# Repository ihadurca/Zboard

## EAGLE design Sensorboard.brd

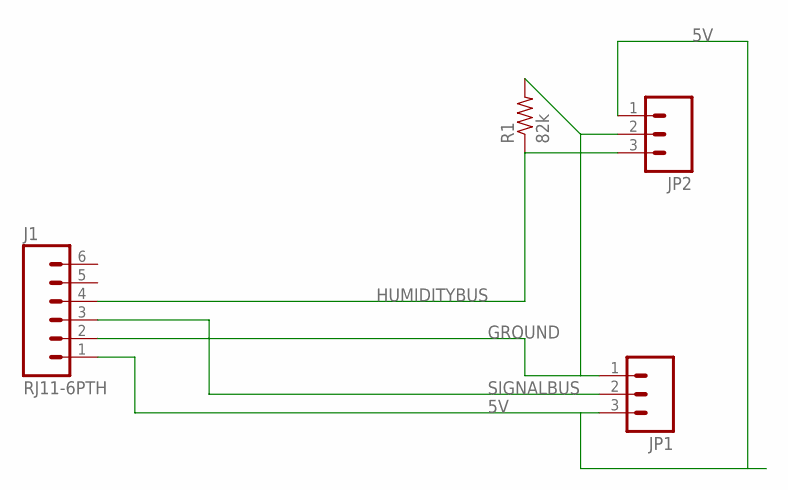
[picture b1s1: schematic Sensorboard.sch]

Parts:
J1: RJ11-6PTH; RJ11-6
JP1, JP2: M03PTH; 1X03
R1: 82k; AXIAL-0.3-KIT

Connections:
5V: J1.1, JP1.3, JP2.1
GROUND: J1.2, JP1.1, JP2.2, R1.P$2 (2)
HUMIDITYBUS: J1.4, JP2.3, R1.P$1 (1)
SIGNALBUS: J1.3, JP1.2

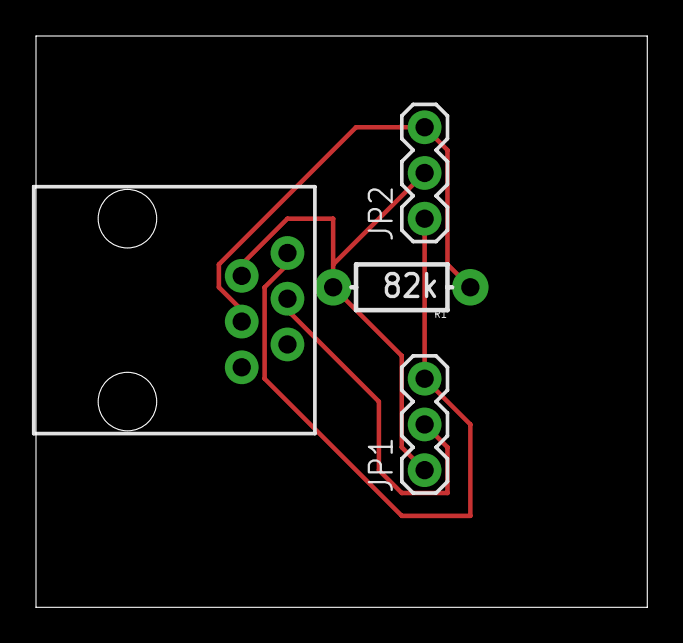
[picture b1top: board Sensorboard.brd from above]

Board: 1 copper layer, 34.0 x 31.7 mm, 4 parts (0 on the bottom side), 4 nets.

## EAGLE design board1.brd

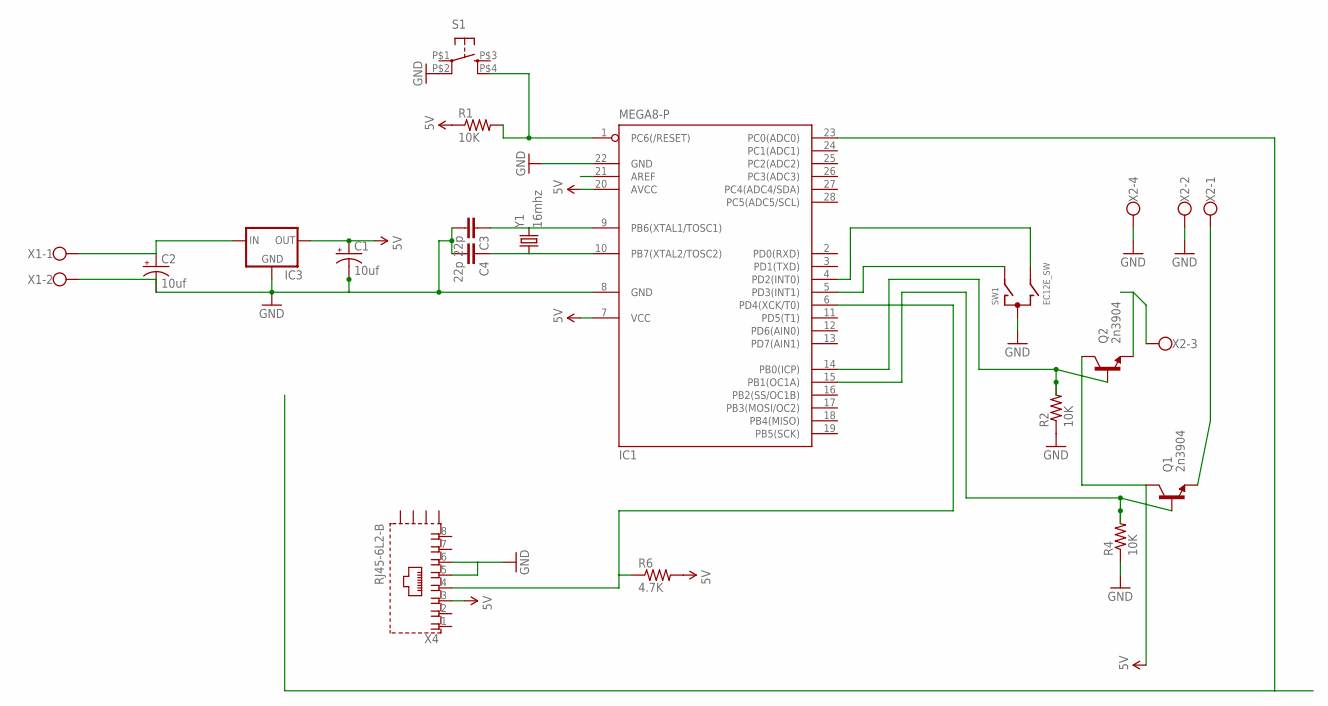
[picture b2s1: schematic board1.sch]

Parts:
C1, C2: 10uf; CPOL-RADIAL-10UF-25V
C3, C4: 22p; AXIAL-5MM
IC1: MEGA8-P; DIL28-3
IC3: V_REG_78XXSINK; TO220-IGO
Q1, Q2: 2n3904; TO-92-AMMO
R1, R2, R4: 10K; AXIAL-0.3
R6: 4.7K; AXIAL-0.3-KIT
S1: TAC_SWITCHKSA_SEALED; KSA_SEALED_TAC_SWITCH
SW1: EC12E_SW; ALPS_EC12E_SW
X1: W237-102
X2: W237-4
X4: RJ45-6L2-B; RJ45-SHIELD2
Y1: 16mhz; HC49US

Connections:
5V: C1.1 (+), IC1.7 (VCC), IC1.20 (AVCC), IC3.OUT, Q1.3 (C), Q2.3 (C), R1.P$1 (1), R6.P$2 (2), X4.3
DALLASONEWIREBUS: IC1.6 (PD4(XCK/T0)), R6.P$1 (1), X4.4
GND: C1.2 (-), C2.2 (-), C3.P$2 (2), C4.P$2 (2), IC1.8 (GND), IC1.22 (GND), IC3.GND, R2.P$1 (1), R4.P$1 (1), S1.P$2 (2), SW1.C, X1.2, X2.2, X2.4, X4.5, X4.6
unnamed: IC1.1 (PC6(/RESET)), R1.P$2 (2), S1.P$4 (4)
unnamed: C2.1 (+), IC3.IN, X1.1
unnamed: C3.P$1 (1), IC1.9 (PB6(XTAL1/TOSC1)), Y1.2
unnamed: C4.P$1 (1), IC1.10 (PB7(XTAL2/TOSC2)), Y1.1
unnamed: IC1.4 (PD2(INT0)), SW1.B
unnamed: IC1.5 (PD3(INT1)), SW1.A
unnamed: IC1.15 (PB1(OC1A)), Q1.2 (B), R4.P$2 (2)
unnamed: Q2.1 (E), X2.3
unnamed: Q1.1 (E), X2.1
unnamed: IC1.14 (PB0(ICP)), Q2.2 (B), R2.P$2 (2)

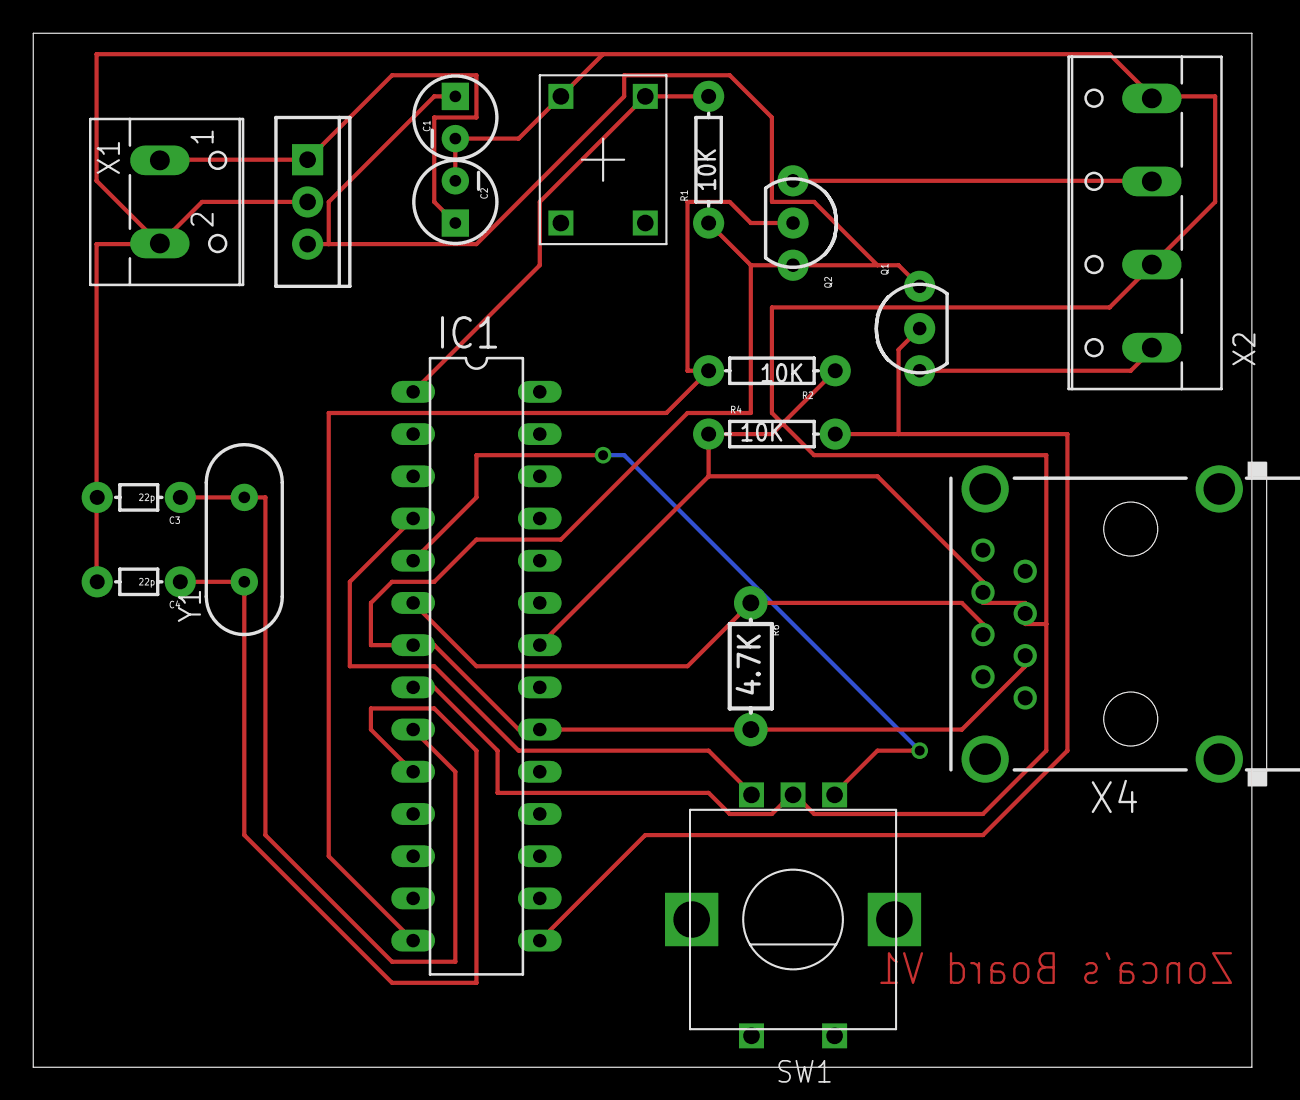
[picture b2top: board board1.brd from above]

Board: 2 copper layers, 74.2 x 62.2 mm, 18 parts (0 on the bottom side), 13 nets.

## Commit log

2012-02-16 Updated board to version 1.1
2012-02-16 no message
2012-02-19 Organizing
2012-02-19 Added Arduino code & dependent libraries
2012-02-19 Removed dup
2012-02-19 Cleaned up code - nlace
2012-02-27 Updated to include 2 adjustment screens for a +/- value for both channels

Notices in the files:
parts and their libraries:
SparkFun: Licensing: CC v3.0 Share-Alike You are welcome to use this library for commercial purposes.
